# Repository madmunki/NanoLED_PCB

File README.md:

# NanoLED_PCB
A PCB for an Arduino Nano controlled WS2812B (16x16 LEDs).

The PCB is safe for up to 5A, if you plan to use more than 5A, add a solder layer or wire on back bridging the +5v pin on the barrel, and the cap.

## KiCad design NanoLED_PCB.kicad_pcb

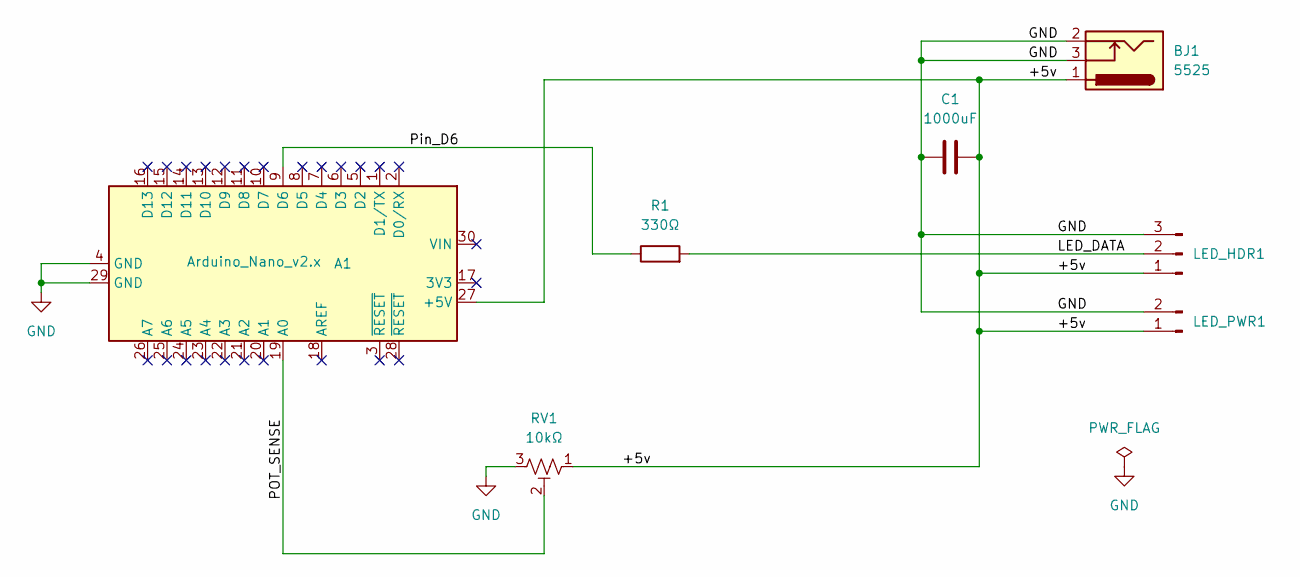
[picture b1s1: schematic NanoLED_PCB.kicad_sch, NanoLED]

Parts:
A1: Arduino_Nano_v2.x; Arduino_Nano
BJ1: 5525; BarrelJack_Horizontal
C1: 1000uF; C_Radial_D8.0mm_H11.5mm_P3.50mm
LED_HDR1: LED_HDR; PinHeader_1x03_P2.54mm_Vertical
LED_PWR1: LED_PWR; PinHeader_1x02_P2.54mm_Vertical
R1: 330Ω; R_Axial_DIN0207_L6.3mm_D2.5mm_P7.62mm_Horizontal
RV1: 10kΩ; Potentiometer_Bourns_3386P_Vertical

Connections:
/+5v: A1.27 (+5V), BJ1.1, C1.2, LED_HDR1.1, LED_PWR1.1, RV1.1
/LED_DATA: LED_HDR1.2, R1.2
/POT_SENSE: A1.19 (A0), RV1.2
/Pin_D6: A1.9 (D6), R1.1
GND: A1.4 (GND), A1.29 (GND), BJ1.2, BJ1.3, C1.1, LED_HDR1.3, LED_PWR1.2, RV1.3

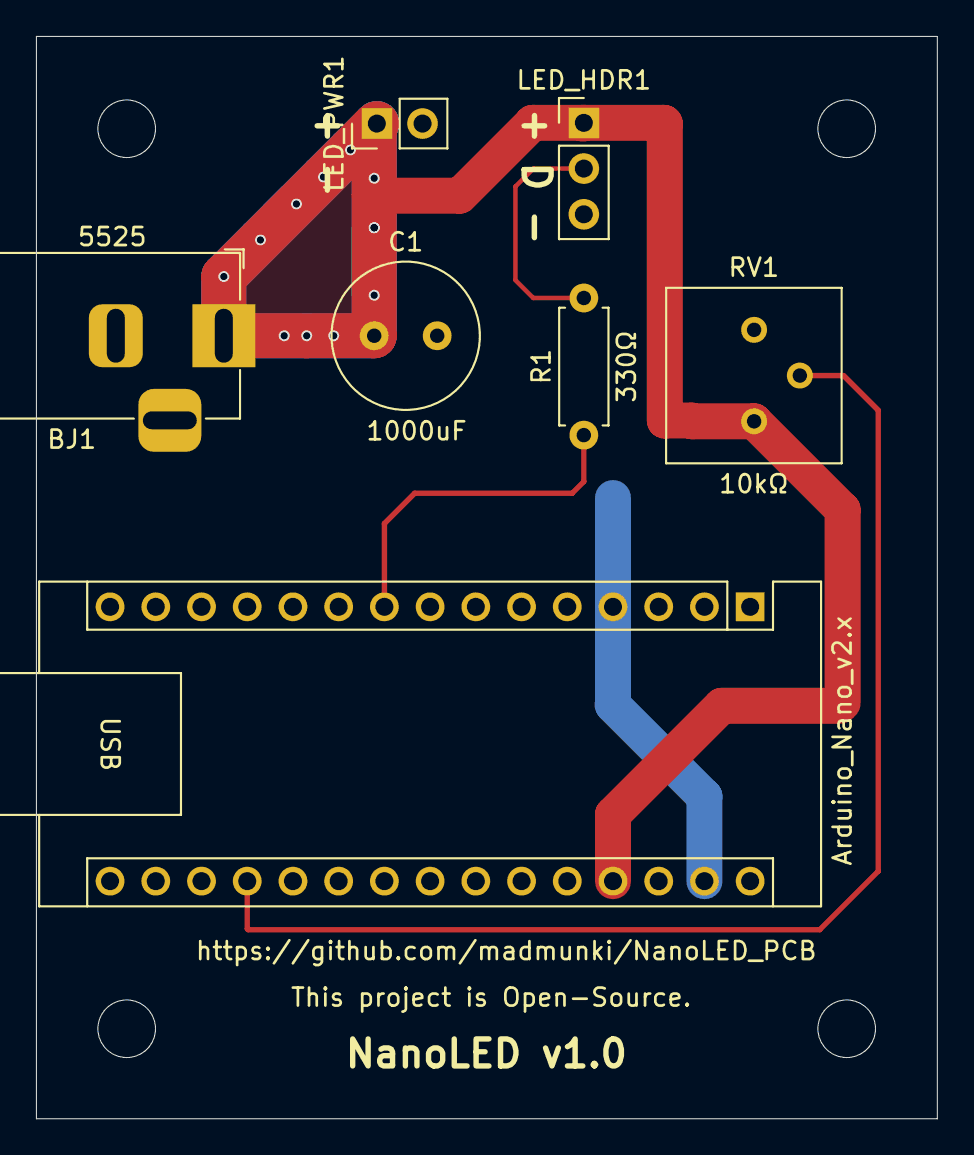
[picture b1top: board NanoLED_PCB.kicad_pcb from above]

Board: 2 copper layers, 50.0 x 60.1 mm, 11 parts (0 on the bottom side), 5 nets.

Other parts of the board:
 : MountingHole_3.2mm_M3
 #2,  #3,  #4: MountingHole_3.2mm_M3

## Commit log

2026-03-24 Updated silkscreen to reflect OSS.
